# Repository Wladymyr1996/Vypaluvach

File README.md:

# Vypaluvach
"Vypaluvach" this is my project of CNC image woodburner

test Branch

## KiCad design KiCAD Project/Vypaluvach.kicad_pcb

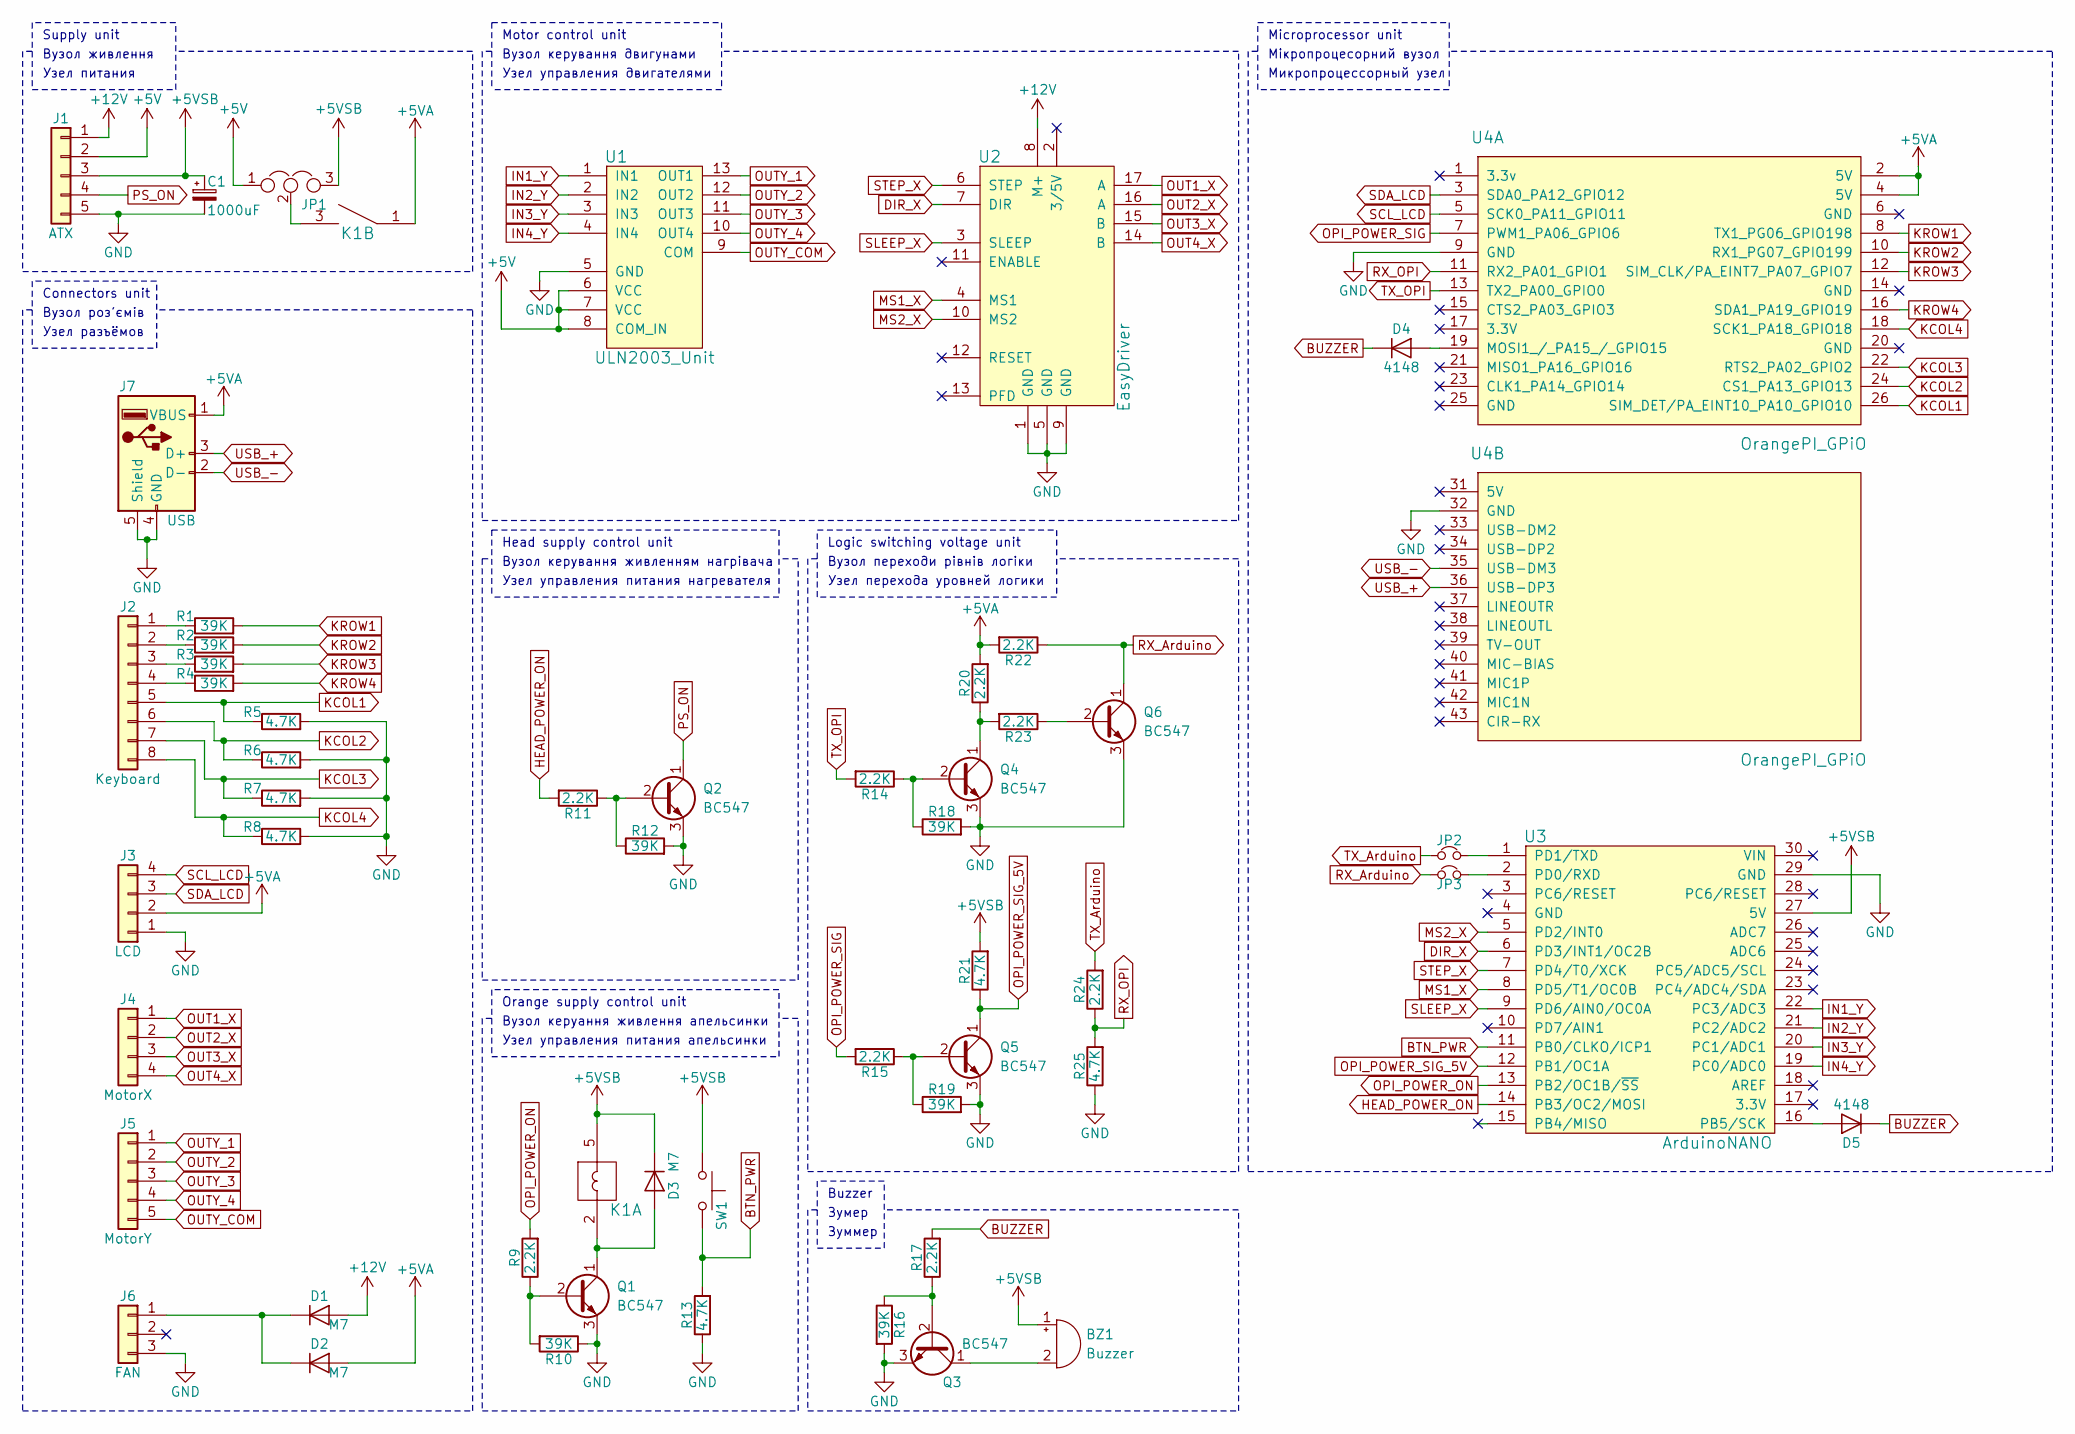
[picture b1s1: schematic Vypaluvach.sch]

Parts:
BZ1: Buzzer; Buzzer_12x9.5RM7.6
C1: 1000uF; CP_Radial_D10.0mm_P5.00mm
D1, D2, D3: M7; DO-214AC
D4, D5: 4148; D_MiniMELF_Handsoldering
J1: ATX; Conn_1x5_d1.5mm
J2: Keyboard; Conn_1x8_d1mm
J3: LCD; Conn_1x4_d1mm
J4: MotorX; Conn_1x4_d1mm
J5: MotorY; Conn_1x5_d1mm
J6: FAN; Conn_1x3_d1mm
J7: USB
JP1: OPIPowerSel; Conn_1x3_d1mm
JP2, JP3: Jumper_NC_Small; Conn_1x2_d1mm
K1: SimpleReley; Relay_SPST_SANYOU_SRD_Series_Form_A
Q1, Q2, Q3, Q4, Q5, Q6: BC547; TO-92_Inline_Wide
R1, R2, R3, R4, R10, R12, R16, R18, R19: 39K; R_0805_HandSoldering
R5, R6, R7, R8, R13, R21, R25: 4.7K; R_1206_HandSoldering
R9, R11, R14, R15, R17, R20, R22, R23, R24: 2.2K; R_1206_HandSoldering
SW1: SW_Push; Conn_1x2_d1.5mm
U1: ULN2003_Unit; ULN2003APG_driver
U2: EasyDriver
U3: ArduinoNANO
U4: OrangePI_GPiO; OrangePi_Zero

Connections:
+5V: J1.2, JP1.1, U1.6 (VCC), U1.7 (VCC), U1.8 (COM_IN)
+5VA: D2.2 (A), J3.2, J7.1 (VBUS), K1.1, R20.2, R22.2, U4.2 (5V), U4.4 (5V)
+5VSB: BZ1.1 (-), C1.1, D3.1 (K), J1.3, JP1.3, K1.5, R21.2, SW1.1, U3.27 (5V)
+12V: D1.2 (A), J1.1, U2.8 (M+)
BTN_PWR: R13.2, SW1.2, U3.11 (PB0/CLKO/ICP1)
BUZZER: D4.1 (K), D5.1 (K), R17.2
DIR_X: U2.7 (DIR), U3.6 (PD3/INT1/OC2B)
GND: C1.2, J1.5, J3.1, J6.3, J7.4 (GND), J7.5 (Shield), Q1.3 (E), Q2.3 (E), Q3.3 (E), Q4.3 (E), Q5.3 (E), Q6.3 (E), R5.2, R6.2, R7.2, R8.2, R10.1, R12.2, R13.1, R16.2, R18.2, R19.2, R25.1, U1.5 (GND), U2.1 (GND), U2.5 (GND), U2.9 (GND), U3.29 (GND), U4.9 (GND), U4.32 (GND)
HEAD_POWER_ON: R11.2, U3.14 (PB3/OC2/MOSI)
IN1_Y: U1.1 (IN1), U3.22 (PC3/ADC3)
IN2_Y: U1.2 (IN2), U3.21 (PC2/ADC2)
IN3_Y: U1.3 (IN3), U3.20 (PC1/ADC1)
IN4_Y: U1.4 (IN4), U3.19 (PC0/ADC0)
KCOL1: J2.5, R5.1, U4.26 (SIM_DET/PA_EINT10_PA10_GPIO10)
KCOL2: J2.6, R6.1, U4.24 (CS1_PA13_GPIO13)
KCOL3: J2.7, R7.1, U4.22 (RTS2_PA02_GPIO2)
KCOL4: J2.8, R8.1, U4.18 (SCK1_PA18_GPIO18)
KROW1: R1.2, U4.8 (TX1_PG06_GPIO198)
KROW2: R2.2, U4.10 (RX1_PG07_GPIO199)
KROW3: R3.2, U4.12 (SIM_CLK/PA_EINT7_PA07_GPIO7)
KROW4: R4.2, U4.16 (SDA1_PA19_GPIO19)
MS1_X: U2.4 (MS1), U3.8 (PD5/T1/OC0B)
MS2_X: U2.10 (MS2), U3.5 (PD2/INT0)
unnamed: BZ1.2 (+), Q3.1 (C)
unnamed: D1.1 (K), D2.1 (K), J6.1
unnamed: D3.2 (A), K1.2, Q1.1 (C)
unnamed: D4.2 (A), U4.19 (MOSI1_/_PA15_/_GPIO15)
unnamed: D5.2 (A), U3.16 (PB5/SCK)
unnamed: J2.1, R1.1
unnamed: J2.2, R2.1
unnamed: J2.3, R3.1
unnamed: J2.4, R4.1
unnamed: JP1.2, K1.3
unnamed: JP2.2, U3.1 (PD1/TXD)
unnamed: JP3.2, U3.2 (PD0/RXD)
unnamed: Q1.2 (B), R9.1, R10.2
unnamed: Q2.2 (B), R11.1, R12.1
unnamed: Q3.2 (B), R16.1, R17.1
unnamed: Q4.1 (C), R20.1, R23.2
unnamed: Q4.2 (B), R14.1, R18.1
unnamed: Q5.2 (B), R15.1, R19.1
unnamed: Q6.2 (B), R23.1
OPI_POWER_ON: R9.2, U3.13 (PB2/OC1B/~SS)
OPI_POWER_SIG: R15.2, U4.7 (PWM1_PA06_GPIO6)
OPI_POWER_SIG_5V: Q5.1 (C), R21.1, U3.12 (PB1/OC1A)
OUT1_X: J4.1, U2.17 (A)
OUT2_X: J4.2, U2.16 (A)
OUT3_X: J4.3, U2.15 (B)
OUT4_X: J4.4, U2.14 (B)
OUTY_1: J5.1, U1.13 (OUT1)
OUTY_2: J5.2, U1.12 (OUT2)
OUTY_3: J5.3, U1.11 (OUT3)
OUTY_4: J5.4, U1.10 (OUT4)
OUTY_COM: J5.5, U1.9 (COM)
PS_ON: J1.4, Q2.1 (C)
RX_Arduino: JP3.1, Q6.1 (C), R22.1
RX_OPI: R24.1, R25.2, U4.11 (RX2_PA01_GPIO1)
SCL_LCD: J3.4, U4.5 (SCK0_PA11_GPIO11)
SDA_LCD: J3.3, U4.3 (SDA0_PA12_GPIO12)
SLEEP_X: U2.3 (SLEEP), U3.9 (PD6/AIN0/OC0A)
STEP_X: U2.6 (STEP), U3.7 (PD4/T0/XCK)
TX_Arduino: JP2.1, R24.2
TX_OPI: R14.2, U4.13 (TX2_PA00_GPIO0)
USB_+: J7.3 (D+), U4.36 (USB-DP3)
USB_-: J7.2 (D-), U4.35 (USB-DM3)

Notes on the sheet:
Вузол живлення
Supply unit
Узел питания
Motor control unit
Вузол керування двигунами
Узел управления двигателями
Microprocessor unit
Мікропроцесорний вузол
Микропроцессорный узел
Logic switching voltage unit
Вузол переходи рівнів логіки
Узел перехода уровней логики
Buzzer
Зумер
Зуммер
Orange supply control unit
Вузол керуання живлення апельсинки
Узел управления питания апельсинки
Connectors unit
Вузол роз'ємів
Узел разъёмов
Head supply control unit
Вузол керування живленням нагрівача
Узел управления питания нагревателя

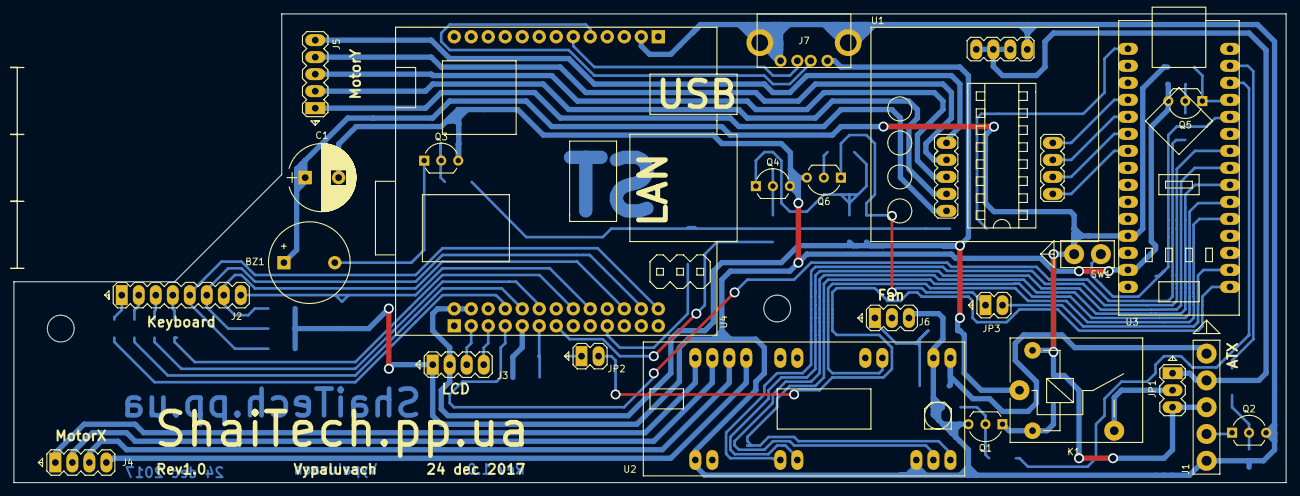
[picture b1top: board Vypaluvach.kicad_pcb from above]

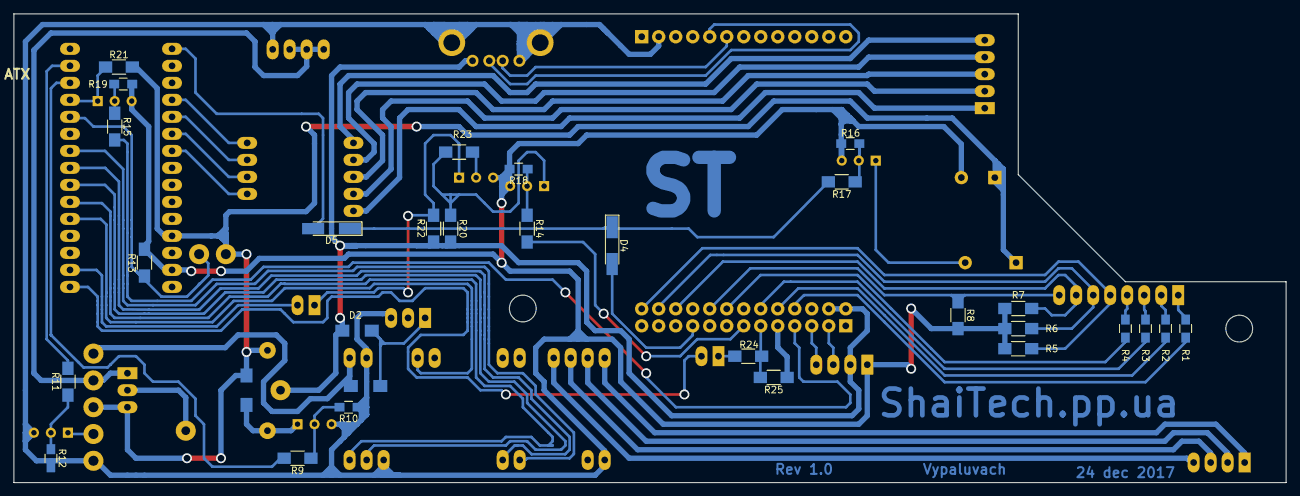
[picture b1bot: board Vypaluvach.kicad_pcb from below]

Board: 2 copper layers, 190.0 x 70.0 mm, 54 parts (30 on the bottom side), 65 nets.

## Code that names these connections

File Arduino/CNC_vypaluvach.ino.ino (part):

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    along with this program.  If not, see <https://www.gnu.org/licenses/>
*/

#define Dir PD3
#define Step PD4
#define Sleep PD6
#define MS1 PD5
#define MS2 PD2

#define BtnPowerSig PB0
#define OPIPowerSig PB1
#define OPIPower PB2
#define HeadPower PB3
#define Buzzer PB5

//Макроси направлення руху двигунів
#define foward 1
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
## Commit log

2018-01-21 New version 2.1-1
2018-01-21 Create empty
2018-01-21 Verison 2.1-1
2018-01-21 Rev 1
2018-01-21 Version 2.1-1
2018-01-21 Rename LICENSE to Server/i2c/LICENSE
2018-01-21 Create LICENSE
2018-01-21 Version 1.7-0
2018-01-26 Adding board PDF
2018-01-28 new version 2.1-2
2018-01-30 new version 2.1-3
2018-01-30 New verison 2.1-3
2018-02-04 new version 2.1-4
2018-02-04 new verison 2.1-4
2019-09-09 Create Nothing
2020-09-03 Added new branch

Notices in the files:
Arduino/CNC_vypaluvach.ino.ino:
Copyright (C) 2017 Volodymyr Stadnyk
This program is free software: you can redistribute it and/or modify
it under the terms of the GNU General Public License as published by
the Free Software Foundation, either version 3 of the License, or
(at your option) any later version.
